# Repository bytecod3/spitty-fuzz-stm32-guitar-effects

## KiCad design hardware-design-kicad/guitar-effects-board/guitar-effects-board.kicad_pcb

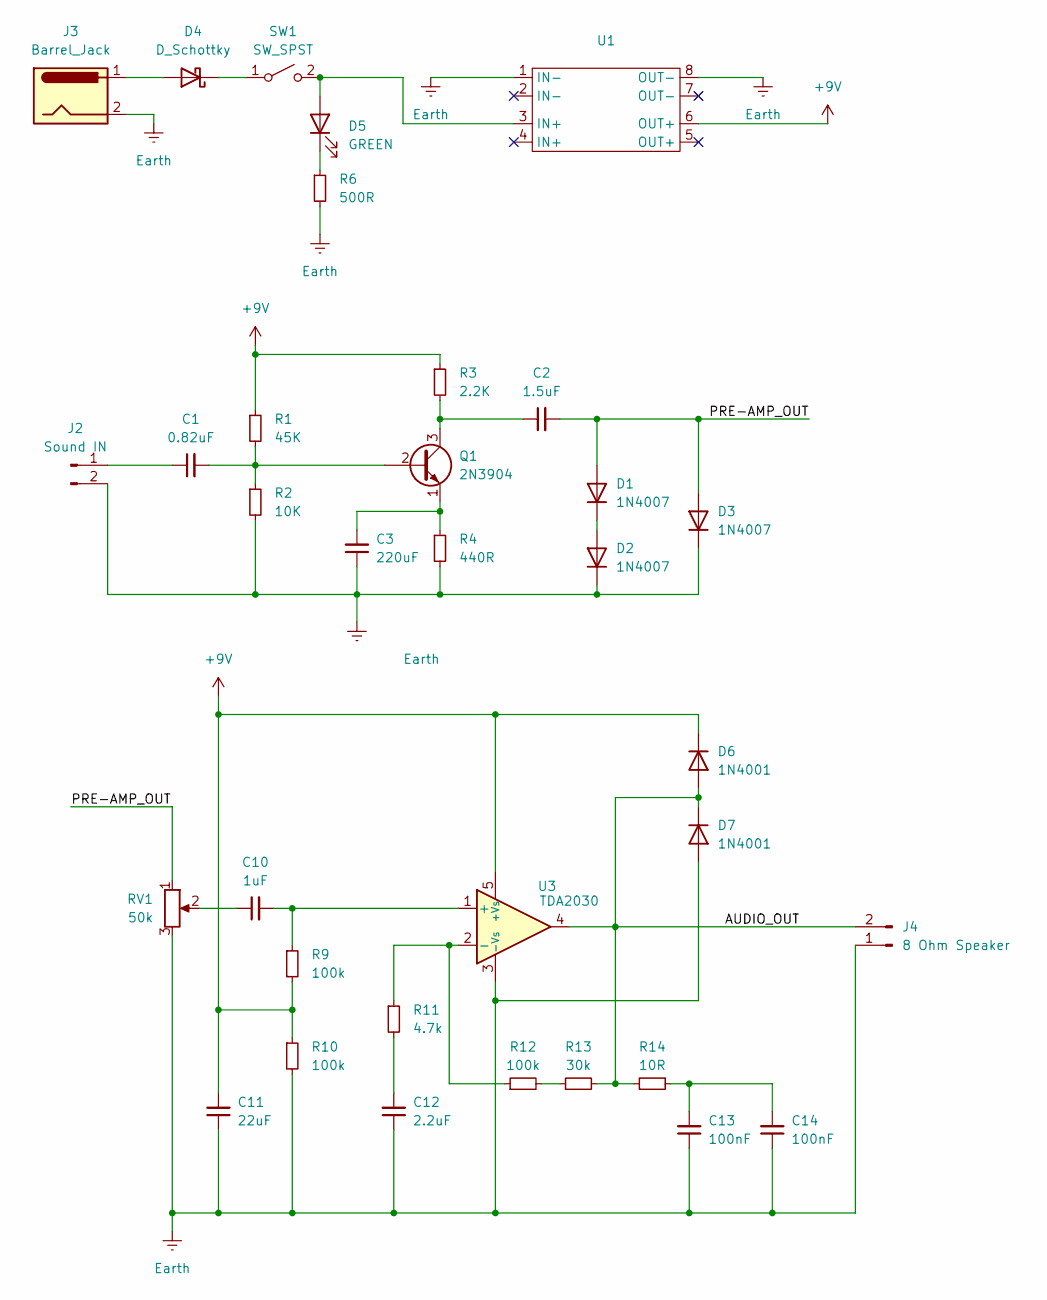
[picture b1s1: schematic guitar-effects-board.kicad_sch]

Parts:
C1: 0.82uF; CP_Radial_D5.0mm_P2.50mm
C2: 1.5uF; CP_Radial_D5.0mm_P2.50mm
C3: 220uF; CP_Radial_D5.0mm_P2.50mm
C10: 1uF; CP_Radial_D5.0mm_P2.50mm
C11: 22uF; CP_Radial_D5.0mm_P2.50mm
C12: 2.2uF; CP_Radial_D5.0mm_P2.50mm
C13, C14: 100nF; CP_Radial_D5.0mm_P2.50mm
D1, D2, D3: 1N4007; D_DO-41_SOD81_P10.16mm_Horizontal
D4: D_Schottky; D_DO-41_SOD81_P10.16mm_Horizontal
D5: GREEN; LED_D3.0mm
D6, D7: 1N4001; D_DO-41_SOD81_P10.16mm_Horizontal
J2: Sound IN; PinHeader_1x02_P2.54mm_Vertical
J3: Barrel_Jack; BarrelJack_GCT_DCJ200-10-A_Horizontal
J4: 8 Ohm Speaker; PinHeader_1x02_P2.54mm_Vertical
Q1: 2N3904; TO-92S_Wide
R1: 45K; R_Axial_DIN0411_L9.9mm_D3.6mm_P20.32mm_Horizontal
R2: 10K; R_Axial_DIN0411_L9.9mm_D3.6mm_P20.32mm_Horizontal
R3: 2.2K; R_Axial_DIN0411_L9.9mm_D3.6mm_P20.32mm_Horizontal
R4: 440R; R_Axial_DIN0411_L9.9mm_D3.6mm_P20.32mm_Horizontal
R6: 500R; R_Axial_DIN0411_L9.9mm_D3.6mm_P20.32mm_Horizontal
R9, R10, R12: 100k; R_Axial_DIN0411_L9.9mm_D3.6mm_P20.32mm_Horizontal
R11: 4.7k; R_Axial_DIN0411_L9.9mm_D3.6mm_P20.32mm_Horizontal
R13: 30k; R_Axial_DIN0411_L9.9mm_D3.6mm_P20.32mm_Horizontal
R14: 10R; R_Axial_DIN0411_L9.9mm_D3.6mm_P20.32mm_Horizontal
RV1: 50k; Potentiometer_Bourns_3386C_Horizontal
SW1: SW_SPST; SW_Slide-03_Wuerth-WS-SLTV_10x2.5x6.4_P2.54mm
U1: MP1584_BUCK_CONVERTER
U3: TDA2030; TO-220-5_P3.4x3.7mm_StaggerOdd_Lead3.8mm_Vertical

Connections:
+9V: C11.2, D6.1 (K), R1.1, R3.1, R9.2, R10.1, U1.6 (OUT+), U3.5 (+Vs)
/AUDIO_OUT: D6.2 (A), D7.1 (K), J4.2, R13.2, R14.2, U3.4
/PRE-AMP_OUT: C2.2, D1.2 (A), D3.2 (A), RV1.1
Earth: C3.1, C11.1, C12.1, C13.1, C14.1, D2.1 (K), D3.1 (K), D7.2 (A), J2.2, J3.2, J4.1, R2.2, R4.2, R6.2, R10.2, RV1.3, U1.1 (IN-), U1.8 (OUT-), U3.3 (-Vs)
unnamed: C10.1, RV1.2
unnamed: C12.2, R11.2
unnamed: C13.2, C14.2, R14.1
unnamed: D1.1 (K), D2.2 (A)
unnamed: D4.2 (A), J3.1
unnamed: D4.1 (K), SW1.1 (A)
unnamed: D5.2 (A), SW1.2 (B), U1.3 (IN+)
unnamed: D5.1 (K), R6.1
unnamed: C1.1, J2.1
unnamed: C1.2, Q1.2 (B), R1.2, R2.1
unnamed: C2.1, Q1.3 (C), R3.2
unnamed: C3.2, Q1.1 (E), R4.1
unnamed: R12.2, R13.1
unnamed: C10.2, R9.1, U3.1 (+)
unnamed: R11.1, R12.1, U3.2 (-)

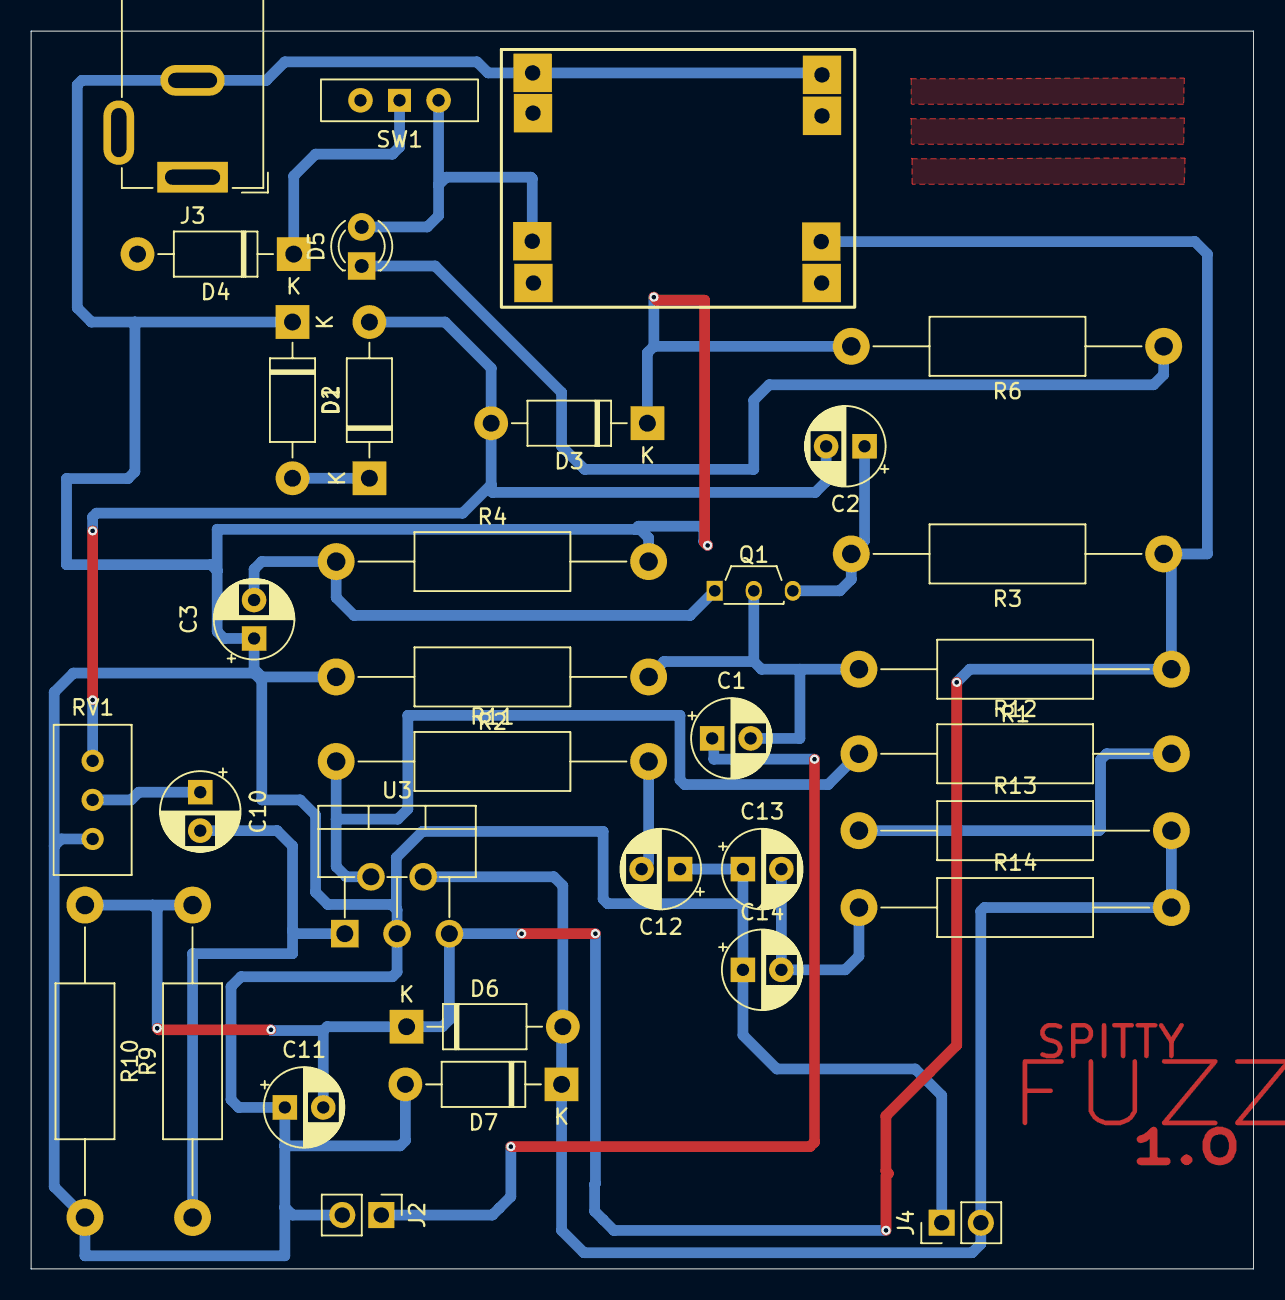
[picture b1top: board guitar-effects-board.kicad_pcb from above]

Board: 2 copper layers, 79.5 x 80.5 mm, 34 parts (0 on the bottom side), 19 nets.

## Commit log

2024-09-25 adds tda circuit
